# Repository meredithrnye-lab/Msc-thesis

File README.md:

# Design and Manufacturing Feasibility Assessment of a Hybrid Jamming Soft Robotic Finger Exoskeleton for Hand Rehabilitation
**This repository contains dissertation work completed in partial fulfillment of the requirements for the degree MSc Rehabilitation Engineering and Assistive Technologies of University College London**

[Dissertation Report](/Reports/Design%20and%20Manufacturing%20Feasibility%20Assessment%20of%20a%20Hybrid%20Jamming%20Soft%20Robotic%20Finger%20Exoskeleton%20for%20Hand%20Rehabilitation.pdf)
authored by [Meredith Nye](https://www.linkedin.com/in/meredith-nye-89455a1b5/), with advisors [Rui Loureiro](https://www.linkedin.com/in/rui-cv-loureiro/) and [Peter Kyberd](https://www.linkedin.com/in/peter-kyberd-b78b1757/)

## Abstract
#### Background and Aims 
Hand impairment 
following stroke, arthritis, and age-related conditions requires high-repetition rehabilitation
that soft robotic exoskeletons are well suited
to deliver. Jamming-based variable-stiffness
mechanisms are promising but underdeveloped, typically offering only single-family, binary stiffness control. This project aimed to
evaluate the design and manufacturing feasibility of a hybrid granular–laminar jamming
soft robotic finger exoskeleton, hypothesising
that hybrid jamming could be integrated into
a compact finger architecture without compromising manufacturability.

#### Methods 
Sixteen design specifications were synthesised from hand exoskeleton literature.
A finger-level prototype was partially built
comprising a fabric pneumatic actuator over
a silicone hybrid jamming module (adapted
from an existing H-block design), with custom PCB control. Actuators were manually
inflated; the jamming module was cast across
four silicone iterations. Each specification was
rated on design and manufacturing axes and
combined into an overall feasibility rating.

#### Results 
The jamming geometry was rated Feasible on the design axis, but all
four casting iterations showed persistent tackiness and incomplete curing at fine layer-pocket
features, so no complete module
was assembled. Fabric actuators inflated with
one demonstrating bending but did not reach
target flexion pressure. No inferential statistics
were applied; findings rest on single-prototype
demonstration and inspection evidence.

#### Summary and Conclusions 
The hybrid jamming specification was rated Not Feasible
overall, only partially supporting the hypothesis. Fine mold geometry and fabrication constraints, not conceptual incompatibility, prevented reliable manufacture. Hybrid jamming
remains a credible route to graduated-stiffness
rehabilitation exoskeletons, but reliable small scale silicone manufacturing must be resolved
before clinical translation.

## Relevant Repository Files
[PCB Gerber Files](/PCB%20Design/Gerbers.zip)

Version 3 Mold Files: [I3_RHM](/Manufacturing/V3_RM.stl), [I3_RHF](/Manufacturing/V3_RF.stl), [I3_LHM](/Manufacturing/V3_LM.stl), [I3_LHF](/Manufacturing/V3_LF.stl)

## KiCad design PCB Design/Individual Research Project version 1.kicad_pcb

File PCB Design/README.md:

# PCB Design
The custom PCB design is made to accommodate all the electronics needed for a
full glove system and uses a Teensy 4.1 micro-controller. It was manufactured by JLCPCB using an FR-4 substrate. 
Components were manually soldered to the board, with the 0805 surface-mount capacitors and TSSOP multiplexer soldered using a reflow process. 

This folder contains the KiCad files and gerber files associated with the first iteration of the PCB design.

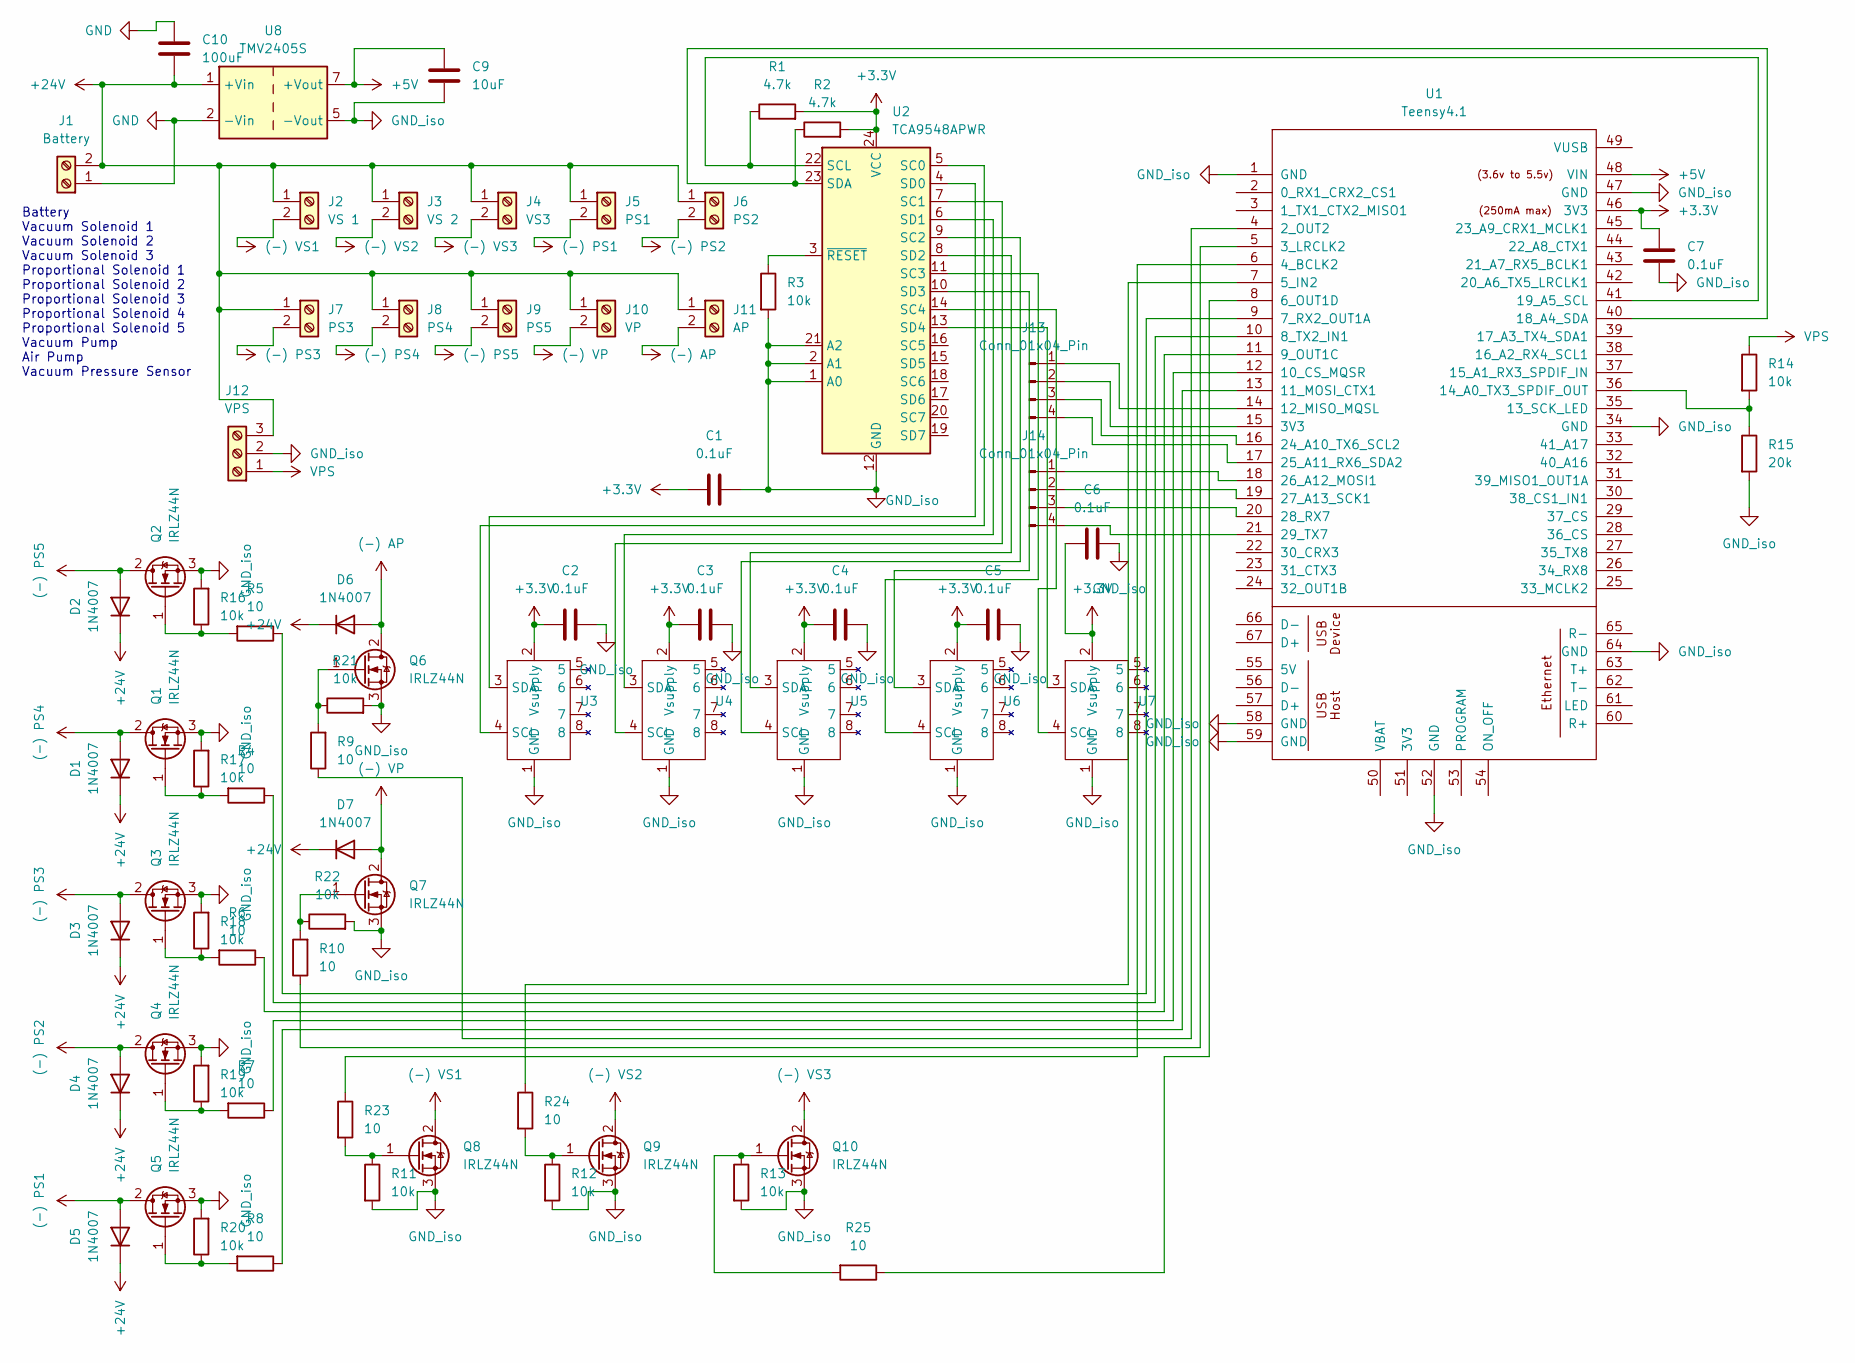
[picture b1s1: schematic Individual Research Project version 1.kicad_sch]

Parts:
C1, C2, C3, C4, C5, C6, C7: 0.1uF; C_0805_2012Metric
C9: 10uF; CP_Radial_Tantal_D5.0mm_P5.00mm
C10: 100uF; CP_Radial_Tantal_D8.0mm_P5.00mm
D1, D2, D3, D4, D5, D6, D7: 1N4007; D_DO-41_SOD81_P10.16mm_Horizontal
J1: Battery; TerminalBlock_Phoenix_MKDS-1,5-2-5.08_1x02_P5.08mm_Horizont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
J2: VS 1; TerminalBlock_Phoenix_MKDS-1,5-2-5.08_1x02_P5.08mm_Horizont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
J3: VS 2; TerminalBlock_Phoenix_MKDS-1,5-2-5.08_1x02_P5.08mm_Horizont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
J4: VS3; TerminalBlock_Phoenix_MKDS-1,5-2-5.08_1x02_P5.08mm_Horizont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
J5: PS1; TerminalBlock_Phoenix_MKDS-1,5-2-5.08_1x02_P5.08mm_Horizont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
J6: PS2; TerminalBlock_Phoenix_MKDS-1,5-2-5.08_1x02_P5.08mm_Horizont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
J7: PS3; TerminalBlock_Phoenix_MKDS-1,5-2-5.08_1x02_P5.08mm_Horizont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
J8: PS4; TerminalBlock_Phoenix_MKDS-1,5-2-5.08_1x02_P5.08mm_Horizont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
J9: PS5; TerminalBlock_Phoenix_MKDS-1,5-2-5.08_1x02_P5.08mm_Horizont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
J10: VP; TerminalBlock_Phoenix_MKDS-1,5-2-5.08_1x02_P5.08mm_Horizont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
J11: AP; TerminalBlock_Phoenix_MKDS-1,5-2-5.08_1x02_P5.08mm_Horizont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
J12: VPS; TerminalBlock_Phoenix_MKDS-1,5-3-5.08_1x03_P5.08mm_Horizont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
J13, J14: Conn_01x04_Pin; JST_PH_B4B-PH-K_1x04_P2.00mm_Vertical
Q1, Q2, Q3, Q4, Q5, Q6, Q7, Q8, Q9, Q10: IRLZ44N; TO-220-3_Vertical
R1, R2: 4.7k; R_Axial_DIN0207_L6.3mm_D2.5mm_P2.54mm_Vertical
R3, R11, R12, R13, R14, R16, R17, R18, R19, R20, R21, R22: 10k; R_Axial_DIN0207_L6.3mm_D2.5mm_P2.54mm_Vertical
R4, R5, R6, R7, R8, R9, R10, R23, R24, R25: 10; R_Axial_DIN0207_L6.3mm_D2.5mm_P2.54mm_Vertical
R15: 20k; R_Axial_DIN0207_L6.3mm_D2.5mm_P2.54mm_Vertical
U1: Teensy4.1; Teensy41
U2: TCA9548APWR; TSSOP-24_4.4x7.8mm_P0.65mm
U3, U4, U5, U6, U7: SSCDANN; SSCAN
U8: TMV2405S; Converter_DCDC_TRACO_TMV-241xS_Single_THT

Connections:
(-) AP: D6.2 (A), J11.2, Q6.2 (D)
(-) PS1: D5.2 (A), J5.2, Q5.2 (D)
(-) PS2: D4.2 (A), J6.2, Q4.2 (D)
(-) PS3: D3.2 (A), J7.2, Q3.2 (D)
(-) PS4: D1.2 (A), J8.2, Q1.2 (D)
(-) PS5: D2.2 (A), J9.2, Q2.2 (D)
(-) VP: D7.2 (A), J10.2, Q7.2 (D)
(-) VS1: J2.2, Q8.2 (D)
(-) VS2: J3.2, Q9.2 (D)
(-) VS3: J4.2, Q10.2 (D)
+3.3V: C1.1, C2.1, C3.1, C4.1, C5.1, C6.1, C7.2, R1.2, R2.2, U1.46 (3V3), U2.24 (VCC), U3.2 (Vsupply), U4.2 (Vsupply), U5.2 (Vsupply), U6.2 (Vsupply), U7.2 (Vsupply)
+5V: C9.2, U1.48 (VIN), U8.7 (+Vout)
+24V: C10.1, D1.1 (K), D2.1 (K), D3.1 (K), D4.1 (K), D5.1 (K), D6.1 (K), D7.1 (K), J1.2, J2.1, J3.1, J4.1, J5.1, J6.1, J7.1, J8.1, J9.1, J10.1, J11.1, J12.3, U8.1 (+Vin)
GND: C10.2, J1.1, U8.2 (-Vin)
GND_iso: C1.2, C2.2, C3.2, C4.2, C5.2, C6.2, C7.1, C9.1, J12.2, Q1.3 (S), Q2.3 (S), Q3.3 (S), Q4.3 (S), Q5.3 (S), Q6.3 (S), Q7.3 (S), Q8.3 (S), Q9.3 (S), Q10.3 (S), R3.2, R11.2, R12.2, R13.2, R15.2, R16.2, R17.2, R18.2, R19.2, R20.2, R21.2, R22.2, U1.1 (GND), U1.34 (GND), U1.47 (GND), U1.52 (GND), U1.58 (GND), U1.59 (GND), U1.64 (GND), U2.1 (A0), U2.2 (A1), U2.12 (GND), U2.21 (A2), U3.1 (GND), U4.1 (GND), U5.1 (GND), U6.1 (GND), U7.1 (GND), U8.5 (-Vout)
unnamed 15: J13.1, U1.14 (12_MISO_MQSL); also elsewhere on the board
unnamed 16: J13.2, U1.15 (3V3); also elsewhere on the board
unnamed 17: J13.3, U1.16 (24_A10_TX6_SCL2); also elsewhere on the board
unnamed 18: J13.4, U1.17 (25_A11_RX6_SDA2); also elsewhere on the board
unnamed 19: J14.1, U1.18 (26_A12_MOSI1); also elsewhere on the board
unnamed 20: J14.2, U1.19 (27_A13_SCK1); also elsewhere on the board
unnamed 21: J14.3, U1.20 (28_RX7); also elsewhere on the board
unnamed 22: J14.4, U1.21 (29_TX7); also elsewhere on the board
unnamed: Q1.1 (G), R4.2, R17.1
unnamed: Q2.1 (G), R5.2, R16.1
unnamed: Q3.1 (G), R6.2, R18.1
unnamed: Q4.1 (G), R7.2, R19.1
unnamed: Q5.1 (G), R8.2, R20.1
unnamed: Q6.1 (G), R9.2, R21.1
unnamed: Q7.1 (G), R10.2, R22.1
unnamed: Q8.1 (G), R11.1, R23.2
unnamed: Q9.1 (G), R12.1, R24.2
unnamed: Q10.1 (G), R13.1, R25.2
unnamed: R9.1, U1.4 (2_OUT2)
unnamed: R10.1, U1.5 (3_LRCLK2)
unnamed: R23.1, U1.6 (4_BCLK2)
unnamed: R24.1, U1.7 (5_IN2)
unnamed: R25.1, U1.8 (6_OUT1D)
unnamed: R5.1, U1.9 (7_RX2_OUT1A)
unnamed: R4.1, U1.10 (8_TX2_IN1)
unnamed: R6.1, U1.11 (9_OUT1C)
unnamed: R7.1, U1.12 (10_CS_MQSR)
unnamed: R8.1, U1.13 (11_MOSI_CTX1)
unnamed: R14.2, R15.1, U1.36 (14_A0_TX3_SPDIF_OUT)
unnamed: R2.1, U1.40 (18_A4_SDA), U2.23 (SDA)
unnamed: R1.1, U1.41 (19_A5_SCL), U2.22 (SCL)
unnamed: U2.5 (SC0), U3.4 (SCL)
unnamed: U2.7 (SC1), U4.4 (SCL)
unnamed: U2.9 (SC2), U5.4 (SCL)
unnamed: U2.11 (SC3), U6.4 (SCL)
unnamed: U2.14 (SC4), U7.4 (SCL)
unnamed: U2.4 (SD0), U3.3 (SDA)
unnamed: U2.6 (SD1), U4.3 (SDA)
unnamed: U2.8 (SD2), U5.3 (SDA)
unnamed: U2.10 (SD3), U6.3 (SDA)
unnamed: U2.13 (SD4), U7.3 (SDA)
unnamed: R3.1, U2.3 (~RESET)
VPS: J12.1, R14.1

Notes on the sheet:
Battery Vacuum Solenoid 1 Vacuum Solenoid 2 Vacuum Solenoid 3 Proportional Solenoid 1 Proportional Solenoid 2 Proportional Solenoid 3 Proportional Solenoid 4 Proportional Solenoid 5 Vacuum Pump Air Pump Vacuum Pressure Sensor

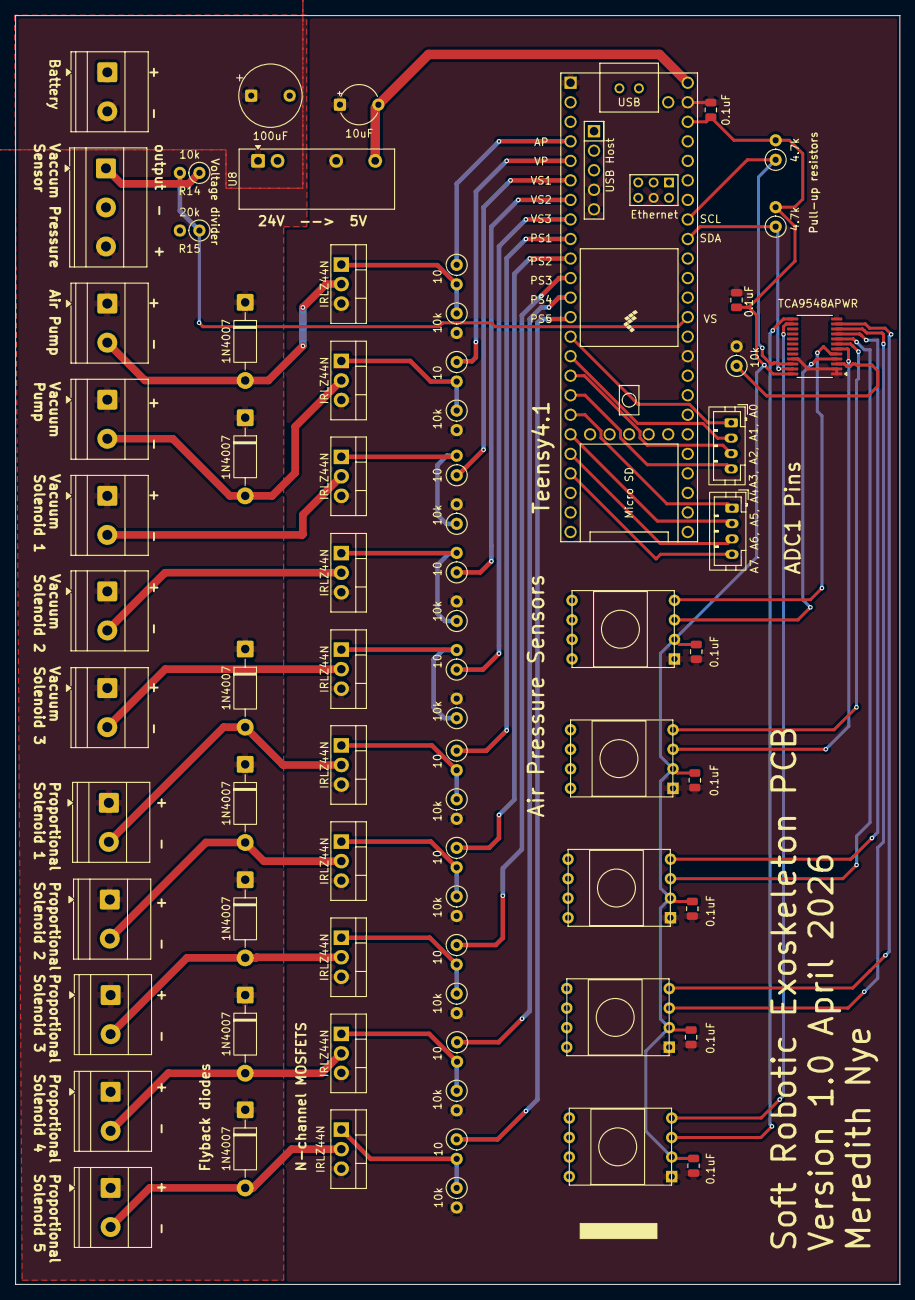
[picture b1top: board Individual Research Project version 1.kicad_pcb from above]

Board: 4 copper layers, 115.0 x 165.0 mm, 73 parts (0 on the bottom side), 58 nets.

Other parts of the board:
A3, A2, A1, A0, A7, A6, A5, A4: Conn_01x04_Pin; JST_PH_B4B-PH-K_1x04_P2.00mm_Vertical

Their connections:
unnamed 15: A3, A2, A1, A0.1; also elsewhere on the board
unnamed 16: A3, A2, A1, A0.2; also elsewhere on the board
unnamed 17: A3, A2, A1, A0.3; also elsewhere on the board
unnamed 18: A3, A2, A1, A0.4; also elsewhere on the board
unnamed 19: A7, A6, A5, A4.1; also elsewhere on the board
unnamed 20: A7, A6, A5, A4.2; also elsewhere on the board
unnamed 21: A7, A6, A5, A4.3; also elsewhere on the board
unnamed 22: A7, A6, A5, A4.4; also elsewhere on the board
